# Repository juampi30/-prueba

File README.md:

## Rele Wifi

## Descripción

El proyecto es una pagina web/aplicación que permita al usuario controlar sus dispositivos electrónicos desde su celular. Este consta de una placa la cual se le conectan los dispositivos, funcionando como un interruptor. De esta forma mediante wifi podes controlar tus aparatos desde la comodidad del celular.

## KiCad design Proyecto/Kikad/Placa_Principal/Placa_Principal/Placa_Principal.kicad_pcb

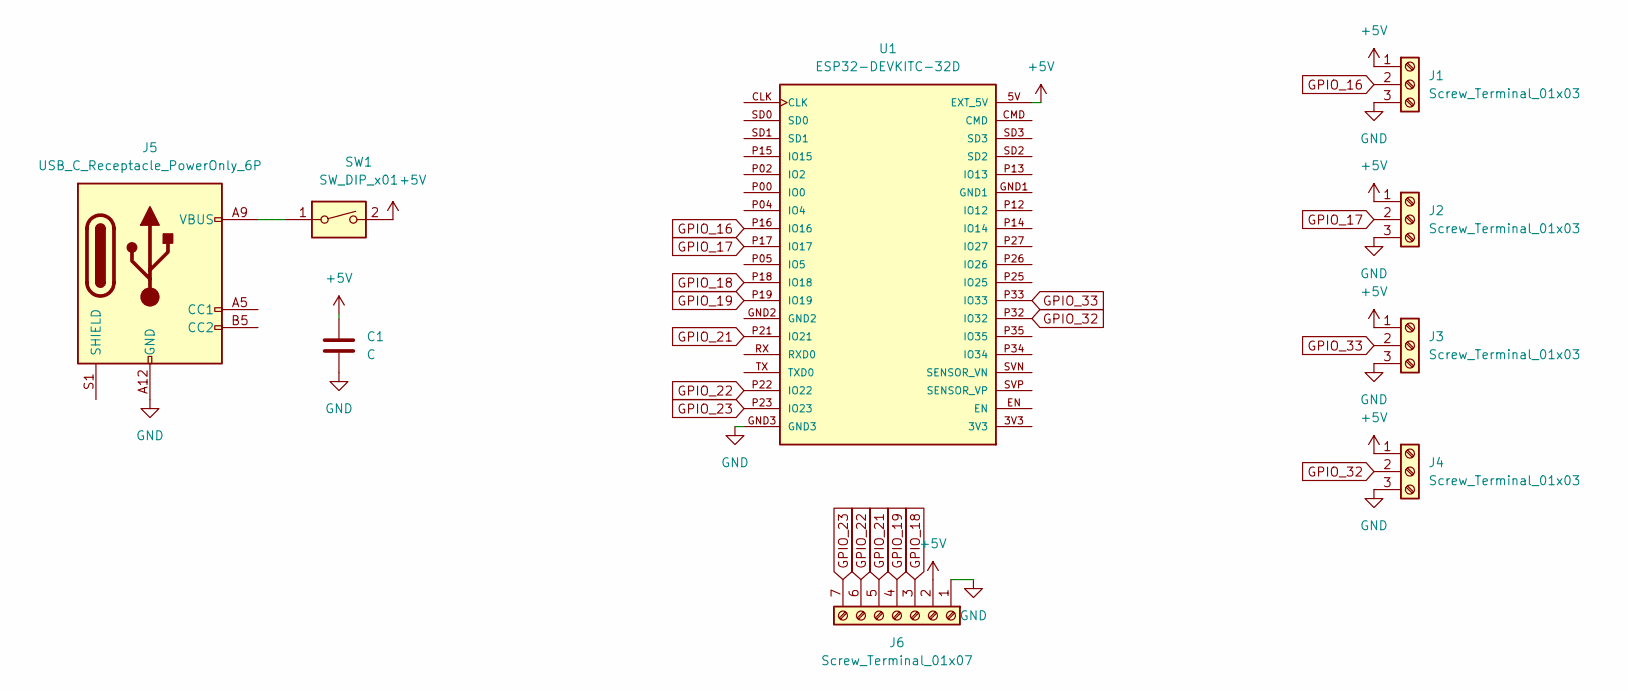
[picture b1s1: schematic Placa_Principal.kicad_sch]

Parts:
C1: C; CP_Radial_D4.0mm_P2.00mm
J1, J2, J3, J4: Screw_Terminal_01x03; PinHeader_1x03_P2.54mm_Vertical
J5: USB_C_Receptacle_PowerOnly_6P; USB_C_Receptacle_GCT_USB4125-xx-x_6P_TopMnt_Horizontal
J6: Screw_Terminal_01x07; PinHeader_1x07_P2.54mm_Vertical
SW1: SW_DIP_x01; PinHeader_1x03_P2.54mm_Vertical
U1: ESP32-DEVKITC-32D; MODULE_ESP32-DEVKITC-32D

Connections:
+5V: C1.2, J1.1, J2.1, J3.1, J4.1, J6.2, SW1.2, U1.5V (EXT_5V)
GND: C1.1, J1.3, J2.3, J3.3, J4.3, J5.A12 (GND), J5.B12 (GND), J6.1, U1.GND3
GPIO_16: J1.2, U1.P16 (IO16)
GPIO_17: J2.2, U1.P17 (IO17)
GPIO_18: J6.3, U1.P18 (IO18)
GPIO_19: J6.4, U1.P19 (IO19)
GPIO_21: J6.5, U1.P21 (IO21)
GPIO_22: J6.6, U1.P22 (IO22)
GPIO_23: J6.7, U1.P23 (IO23)
GPIO_32: J4.2, U1.P32 (IO32)
GPIO_33: J3.2, U1.P33 (IO33)
unnamed: J5.A9 (VBUS), J5.B9 (VBUS), SW1.1

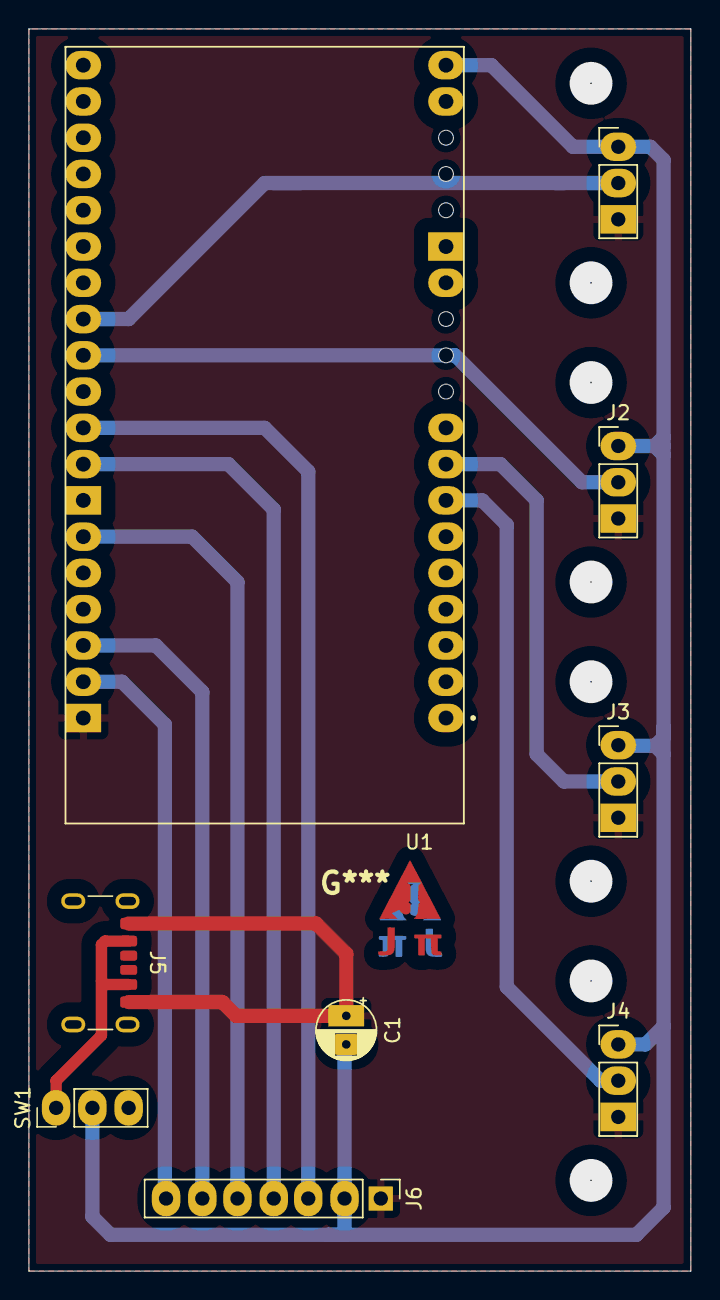
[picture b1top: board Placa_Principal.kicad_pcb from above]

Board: 2 copper layers, 46.4 x 87.0 mm, 9 parts (0 on the bottom side), 12 nets.

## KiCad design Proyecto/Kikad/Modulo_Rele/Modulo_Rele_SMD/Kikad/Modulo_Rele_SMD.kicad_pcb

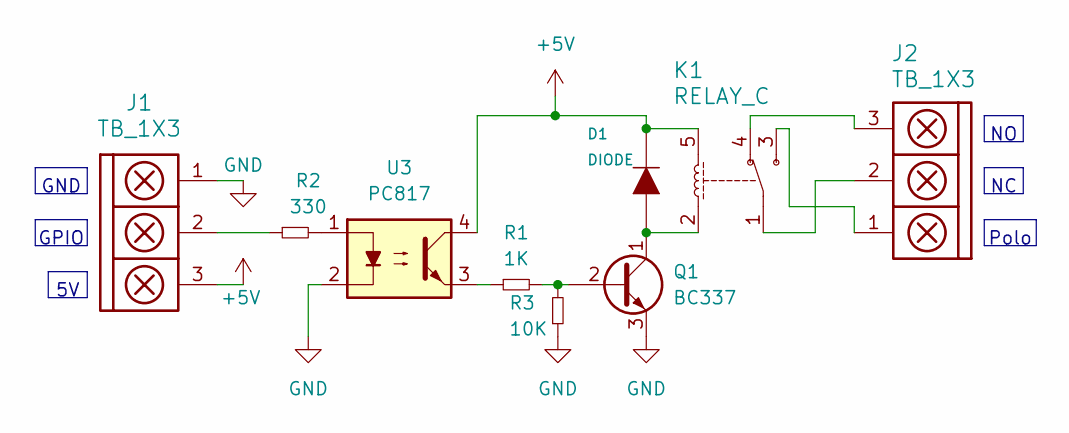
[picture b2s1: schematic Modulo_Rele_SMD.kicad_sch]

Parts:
D1: DIODE; D_SMA
J1: TB_1X3; Molex_KK-254_AE-6410-03A_1x03_P2.54mm_Vertical
J2: TB_1X3; TerminalBlock_bornier-3_P5.08mm
K1: RELAY_C; Relay_SPDT_SANYOU_SRD_Series_Form_C
Q1: BC337; SOT-23
R1: 1K; D_0805_2012Metric
R2: 330; D_0805_2012Metric
R3: 10K; R_0805
U3: PC817; SSO-4_6.7x5.1mm_P2.54mm_Clearance8mm

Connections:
+5V: D1.2 (K), J1.3, K1.5, U3.4
GND: J1.1, Q1.3 (E), R3.1, U3.2
unnamed: D1.1 (A), K1.2, Q1.1 (C)
unnamed: J1.2, R2.1
unnamed: J2.1, K1.3
unnamed: J2.2, K1.1
unnamed: J2.3, K1.4
unnamed: Q1.2 (B), R1.2, R3.2
unnamed: R1.1, U3.3
unnamed: R2.2, U3.1

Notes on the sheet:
GND
GPIO
Polo

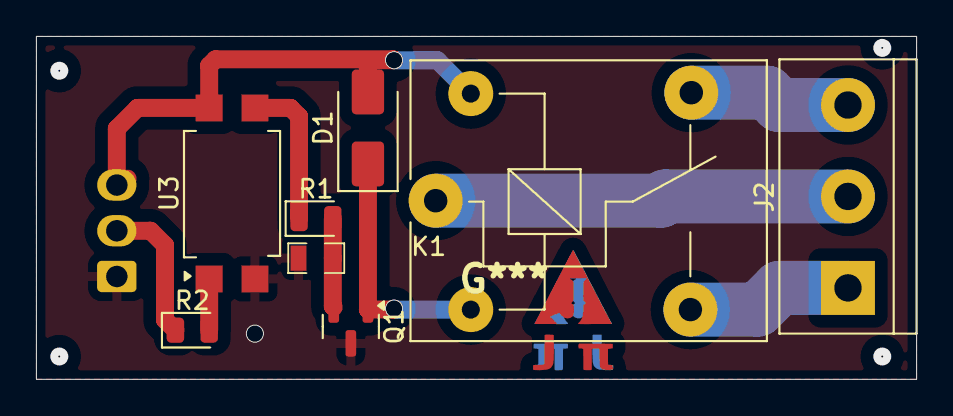
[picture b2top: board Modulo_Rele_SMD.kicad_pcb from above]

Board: 2 copper layers, 48.9 x 19.0 mm, 9 parts (1 on the bottom side), 10 nets.

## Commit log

2025-04-03 mi primer commit
2025-04-03 segundo commit
2025-04-10 Cambie unos componentes en el informe y empece con el kicad del proyefcto(el esquematico del rele)
2025-04-14 cambio en el informe, colocacion de huellas del rele y inicio del PCB
2025-04-14 arreglo errores de git
2025-04-18 Termine el pcb y agregue una carpeta de Extras (imagenes y logo)
2025-04-18 Arregle el logo y puse imagenes de una vista previa
2025-04-18 Hice el Modulo_Rele con SMD y adjunte las imagenes del mismo
2025-04-29 hice el Rele Mixto y adjunte sus imagenes. ademas agregue la resistencia de 10K
2025-05-05 Agregue la carpeta Placa_Principal e hice unas correcciones en el Modulo_Rele
2025-05-06 Hice la Placa_Principal y corregi algunos detalles de la placa modulo rele
2025-05-12 Probando Reedme
    Estoy intentando de hacer un reedme
2025-05-29 Arregle unas cosas de las dos placas
2025-05-30 Cambie unos gpio de la placa principal
2025-05-30 Cambie 2 gpio
2025-05-30 Cambie los gpio y agregue un exel
